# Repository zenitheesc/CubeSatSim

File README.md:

<h1 align="center" style="color:white; background-color:black">CubeSatSim</h1>

<a href="https://github.com/zenitheesc/CubeSatSim/tree/ZenithSatSim#-controle-"><h2> Controle </h2></a>

Para o controle destas placas podem ser utilizado um ESP32 Devkit V1 ou uma Raspberry Pi Zero.

ESP32 DevKit V1 (30 pinos)

-UART: GPIO1 (TX0) e GPIO3 (RX0)

-I2C: GPIO21 (SDA) e GPIO22 (SCL)

-SPI: GPIO12 (MISO), GPIO13 (MOSI), GPIO14 (SCK) e GPIO15 (CS)

Raspberry Pi Zero

-UART: GPIO14 (TX0) e GPIO15 (RX0)

-I2C: GPIO2 (SDA) e GPIO3 (SCL)

-SPI: GPIO9 (MISO), GPIO10 (MOSI), GPIO11 (SCK) e GPIO8 (CS)

Módulo Micro SD Card (comunicação SPI)

<a href="https://github.com/zenitheesc/CubeSatSim/tree/ZenithSatSim#comunica%C3%A7%C3%A3o-e-sensoriamento"><h2>Comunicação e Sensoriamento</h2></a>
E32-433T20DC Módulo LoRa

IMU6050 - Acelerômetro e Giroscópio (comunicação I2C)

BMP280 - Sensor de pressão e temperatura (comunicação I2C)

HDC1080 - Sensor de temperatura e umidade (comunicação I2C)

E32-433T20D - Módulo RF Wireless LoRa 433MHZ (comunicação UART)

<a href="https://github.com/zenitheesc/CubeSatSim/tree/ZenithSatSim#energia"><h2>Energia</h2></a>

LM2596 - Conversor Buck (3.3V)

LED  para indicar 3.3V

XL6009E1 - Conversor Boost (5V)

LED  para indicar 5V

TP4056 - Carregador da bateria

INA219 - Sensor de corrente e tensão DC (comunicação I2C)

Conector Borne para a bateria

Bateria de Litio (3.7V)

<a href="https://github.com/zenitheesc/CubeSatSim/tree/ZenithSatSim#energia"><h2>Lista de Componentes</h2></a>

<p align="center">

</p>
<p align = "center">

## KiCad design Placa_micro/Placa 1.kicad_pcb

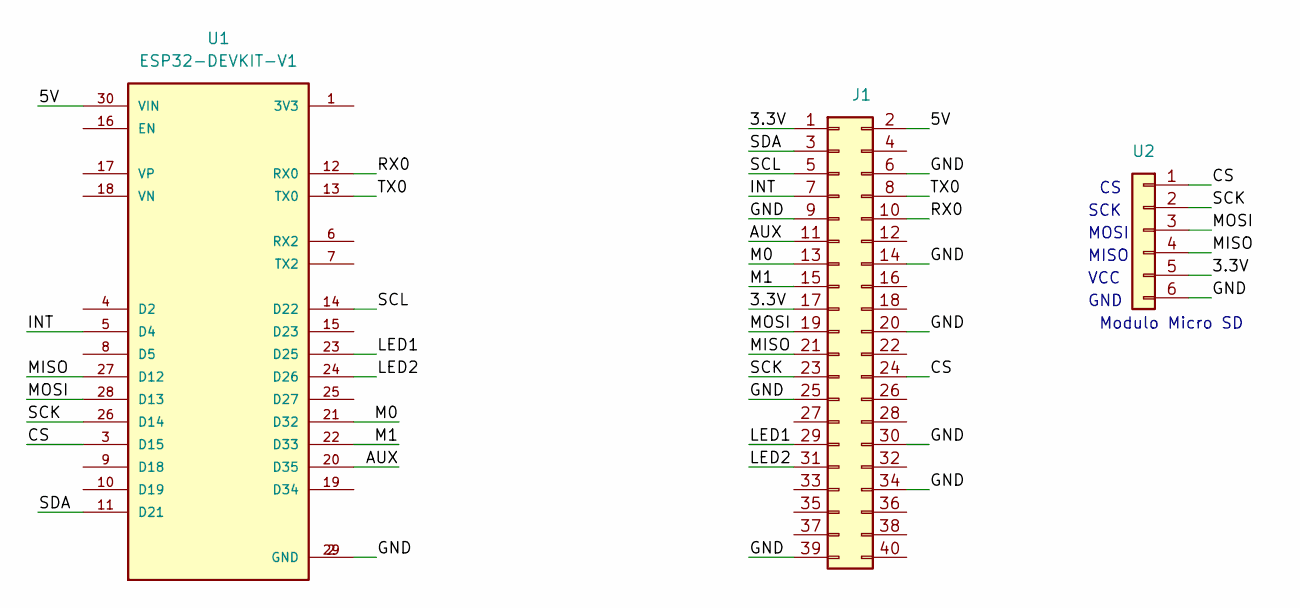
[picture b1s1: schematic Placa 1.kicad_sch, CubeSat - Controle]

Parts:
J1: Conn_02x20_Odd_Even; OBSAT-Board
U1: ESP32-DEVKIT-V1; ESP32_DEVKIT_V1_sem; PARTREV N/A
U2: Conn_01x06; PinSocket_1x06_P2.54mm_Horizontal

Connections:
/3.3V: J1.1, J1.17, U2.5
/5V: J1.2, U1.30 (VIN)
/AUX: J1.11, U1.20 (D35)
/CS: J1.24, U1.3 (D15), U2.1
/GND: J1.6, J1.9, J1.14, J1.20, J1.25, J1.30, J1.34, J1.39, U1.2 (GND), U1.29 (GND), U2.6
/INT: J1.7, U1.5 (D4)
/LED1: J1.29, U1.23 (D25)
/LED2: J1.31, U1.24 (D26)
/M0: J1.13, U1.21 (D32)
/M1: J1.15, U1.22 (D33)
/MISO: J1.21, U1.27 (D12), U2.4
/MOSI: J1.19, U1.28 (D13), U2.3
/RX0: J1.10, U1.12 (RX0)
/SCK: J1.23, U1.26 (D14), U2.2
/SCL: J1.5, U1.14 (D22)
/SDA: J1.3, U1.11 (D21)
/TX0: J1.8, U1.13 (TX0)

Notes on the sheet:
VCC
GND
Modulo Micro SD
MISO
SCK
MOSI

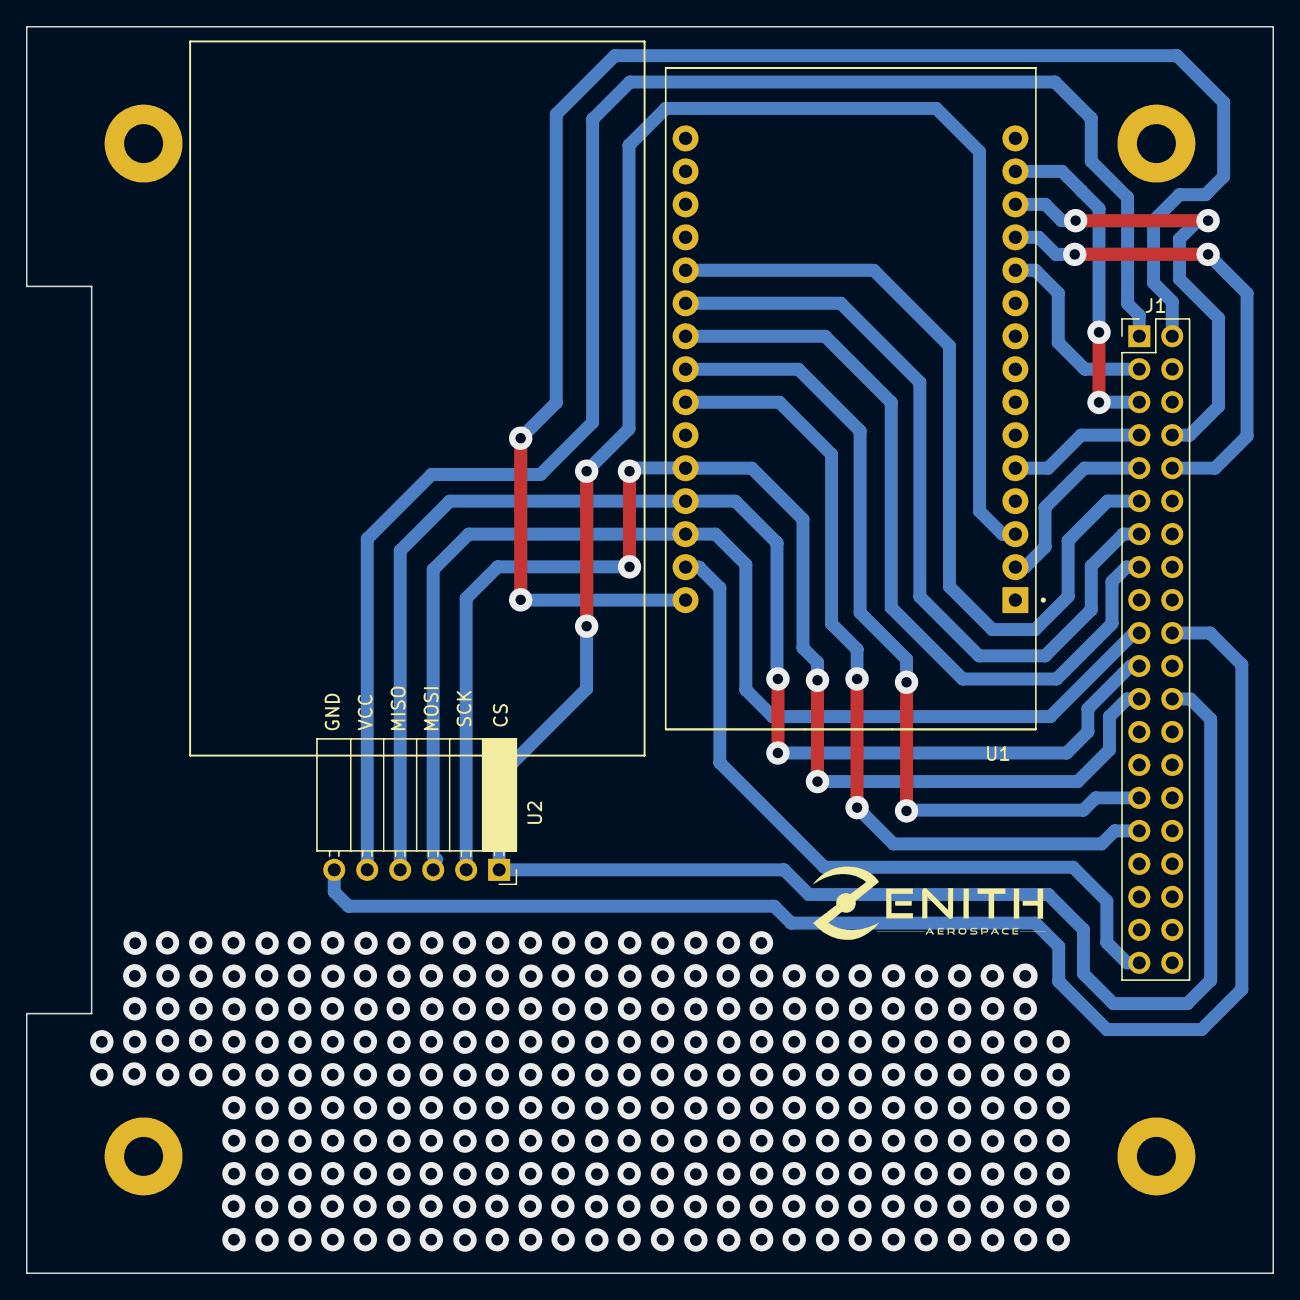
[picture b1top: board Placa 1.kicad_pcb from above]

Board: 2 copper layers, 96.0 x 96.0 mm, 3 parts (0 on the bottom side), 17 nets.

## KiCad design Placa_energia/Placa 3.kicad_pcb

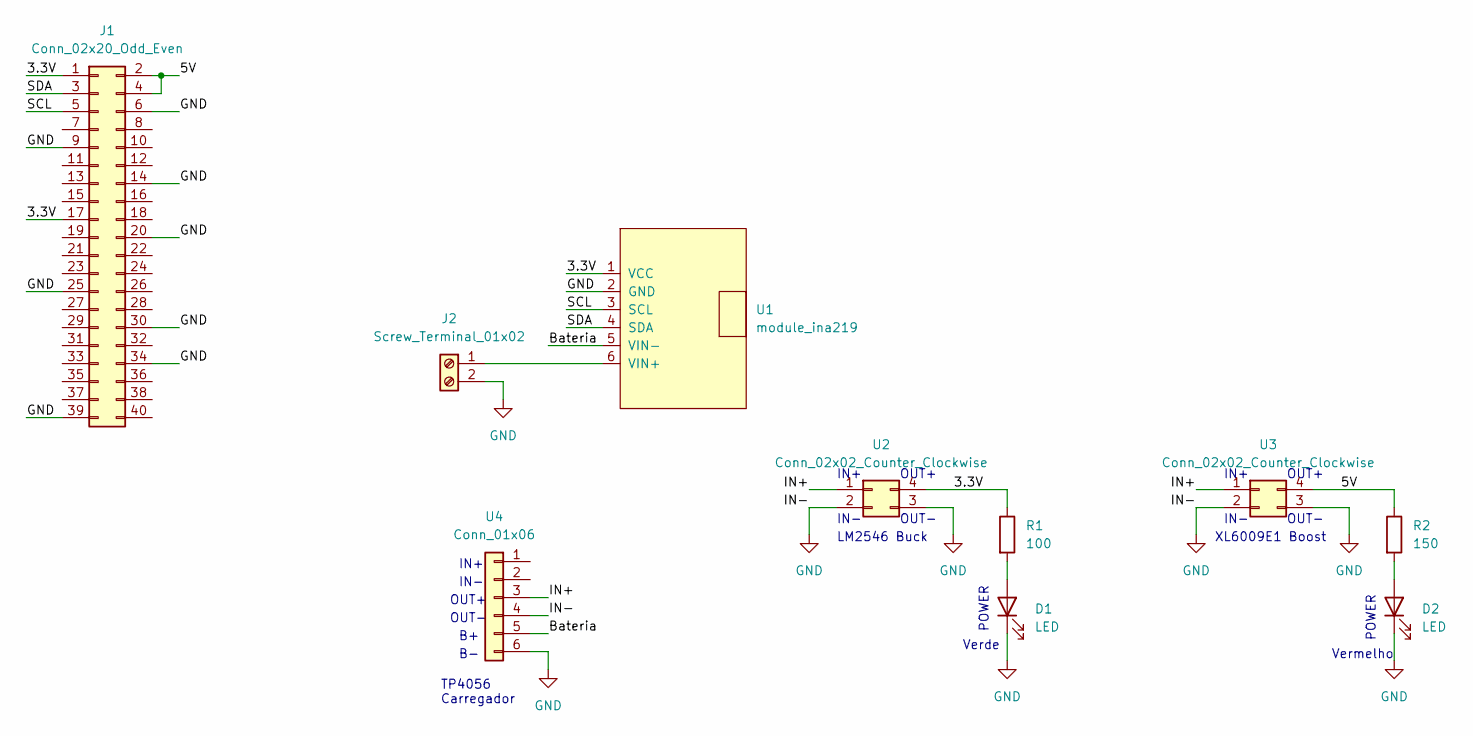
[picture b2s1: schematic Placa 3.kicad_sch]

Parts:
D1, D2: LED; LED_D5.0mm
J1: Conn_02x20_Odd_Even; OBSAT-Board
J2: Screw_Terminal_01x02; TerminalBlock_4Ucon_1x02_P3.50mm_Horizontal
R1: 100; R_Axial_DIN0204_L3.6mm_D1.6mm_P7.62mm_Horizontal
R2: 150; R_Axial_DIN0204_L3.6mm_D1.6mm_P7.62mm_Horizontal
U1: module_ina219
U2, U3: Conn_02x02_Counter_Clockwise; XL6009-Module
U4: Conn_01x06; TP4056-Module

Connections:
/3.3V: J1.1, J1.17, R1.1, U1.1 (VCC), U2.4
/5V: J1.2, J1.4, R2.1, U3.4
/Bateria: U1.5 (VIN-), U4.5
/IN+: U2.1, U3.1, U4.3
/SCL: J1.5, U1.3 (SCL)
/SDA: J1.3, U1.4 (SDA)
GND: D1.1 (K), D2.1 (K), J1.6, J1.9, J1.14, J1.20, J1.25, J1.30, J1.34, J1.39, J2.2, U1.2 (GND), U2.2, U2.3, U3.2, U3.3, U4.4, U4.6
unnamed: D1.2 (A), R1.2
unnamed: D2.2 (A), R2.2
unnamed: J2.1, U1.6 (VIN+)

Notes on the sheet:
Verde
Vermelho
OUT+
LM2546 Buck
POWER
XL6009E1 Boost
IN-
OUT-
IN+
TP4056 Carregador

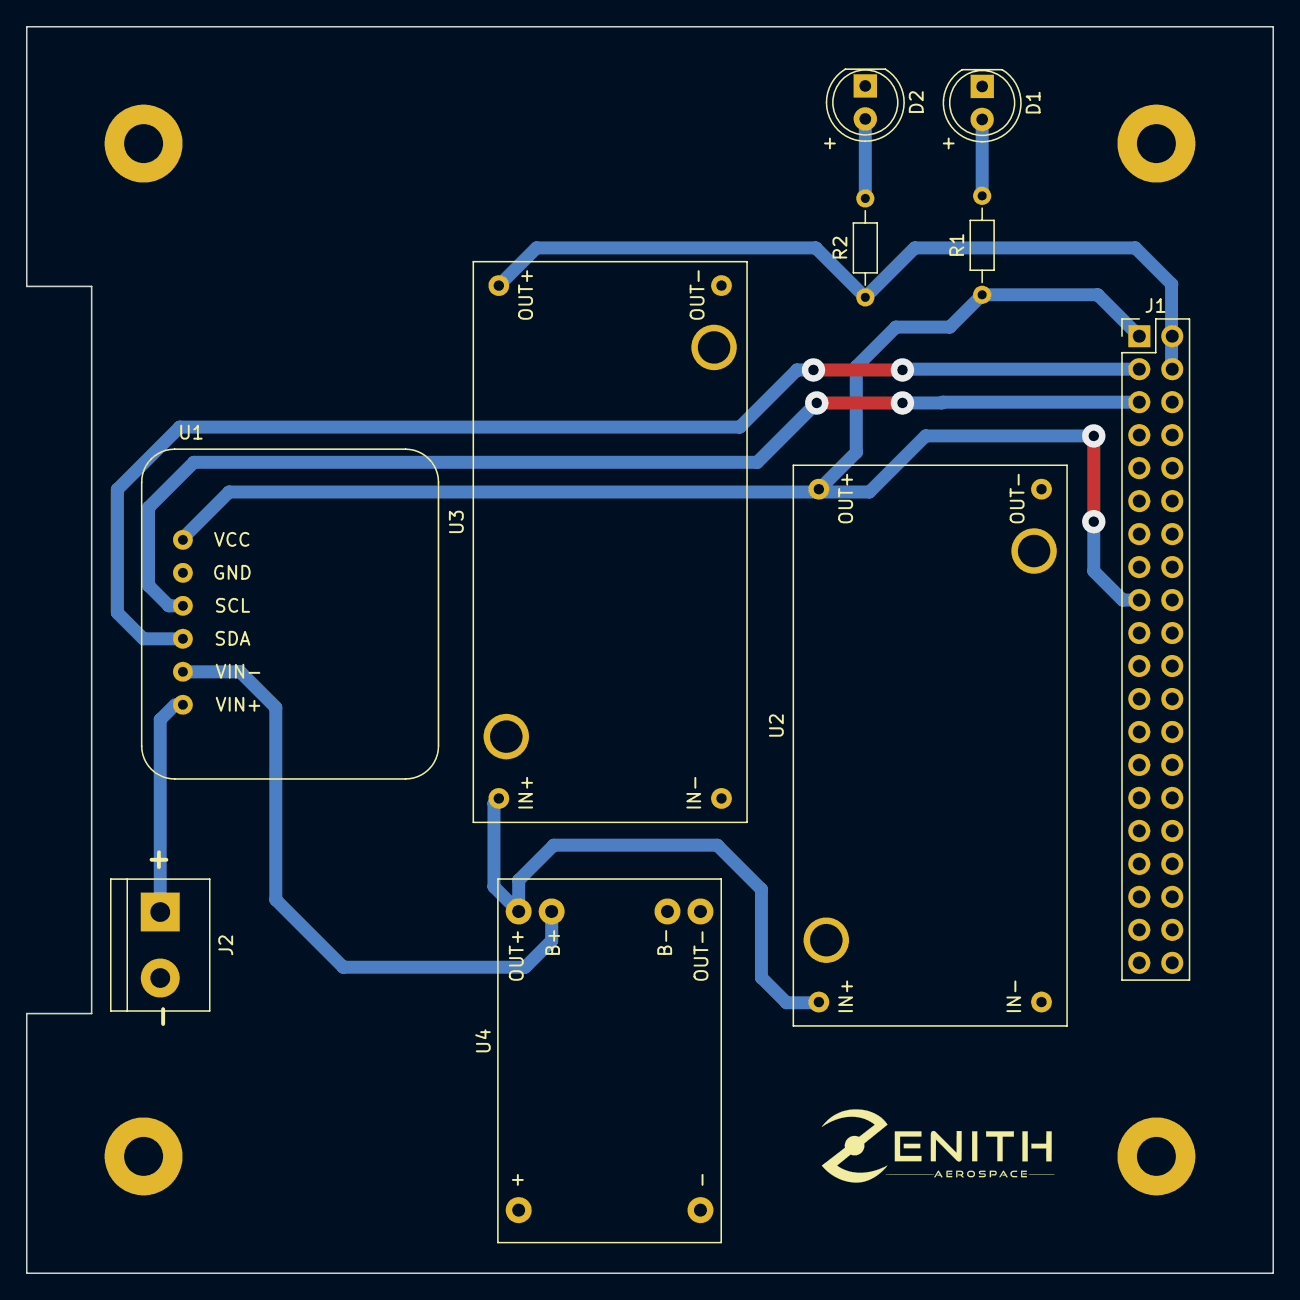
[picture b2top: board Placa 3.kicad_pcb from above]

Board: 2 copper layers, 96.0 x 96.0 mm, 10 parts (0 on the bottom side), 10 nets.

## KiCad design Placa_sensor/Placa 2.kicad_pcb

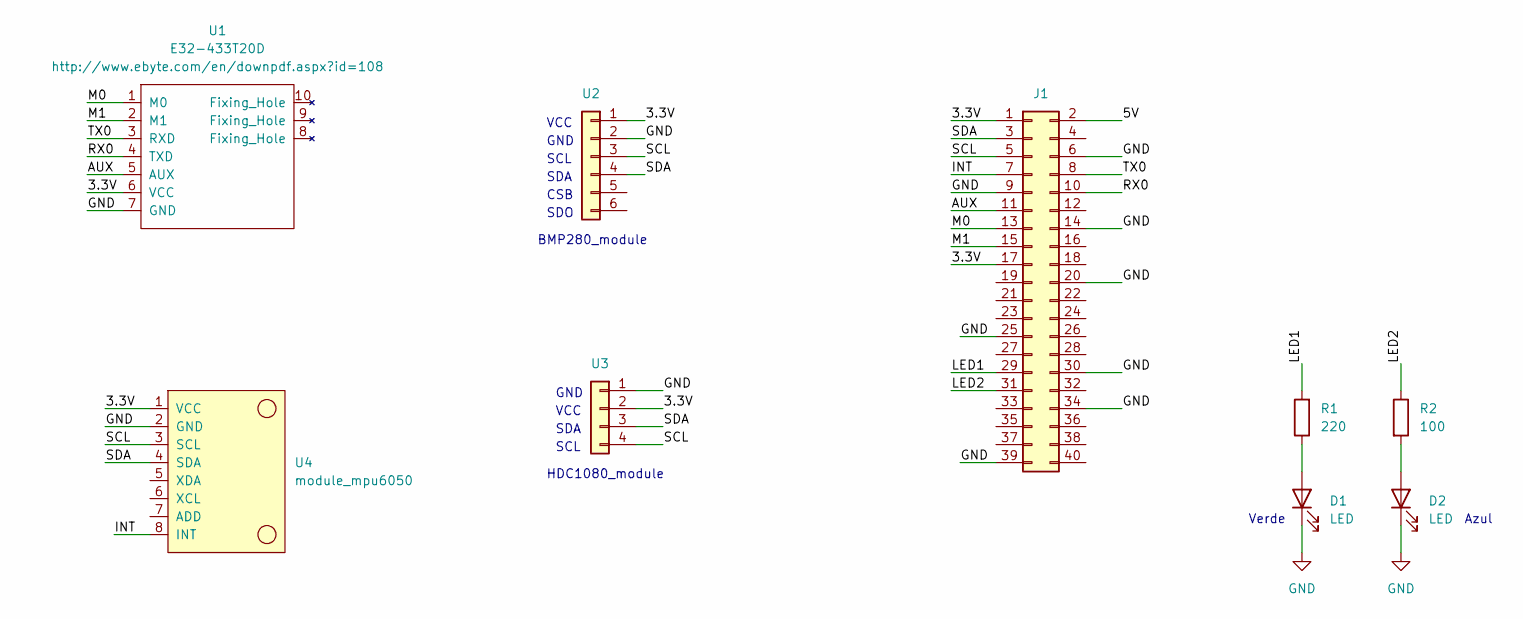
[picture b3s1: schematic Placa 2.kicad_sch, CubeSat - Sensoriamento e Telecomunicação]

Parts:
D1, D2: LED; LED_D5.0mm
J1: Conn_02x20_Odd_Even; OBSAT-Board
R1: 220; R_Axial_DIN0204_L3.6mm_D1.6mm_P7.62mm_Horizontal
R2: 100; R_Axial_DIN0204_L3.6mm_D1.6mm_P7.62mm_Horizontal
U1: E32-433T20D; E32-xxxT20D
U2: Conn_01x06; PinSocket_1x06_P2.54mm_Vertical
U3: Conn_01x04; PinSocket_1x04_P2.54mm_Vertical
U4: module_mpu6050

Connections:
/3.3V: J1.1, J1.17, U1.6 (VCC), U2.1, U3.2, U4.1 (VCC)
/5V: J1.2
/AUX: J1.11, U1.5 (AUX)
/INT: J1.7, U4.8 (INT)
/LED1: J1.29, R1.2
/LED2: J1.31, R2.1
/M0: J1.13, U1.1 (M0)
/M1: J1.15, U1.2 (M1)
/RX0: J1.10, U1.4 (TXD)
/SCL: J1.5, U2.3, U3.4, U4.3 (SCL)
/SDA: J1.3, U2.4, U3.3, U4.4 (SDA)
/TX0: J1.8, U1.3 (RXD)
GND: D1.1 (K), D2.1 (K), J1.6, J1.9, J1.14, J1.20, J1.25, J1.30, J1.34, J1.39, U1.7 (GND), U2.2, U3.1, U4.2 (GND)
unnamed: D1.2 (A), R1.1
unnamed: D2.2 (A), R2.2

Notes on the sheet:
SDO
CSB
SCL
SDA
BMP280_module
GND
HDC1080_module
VCC
Azul
Verde

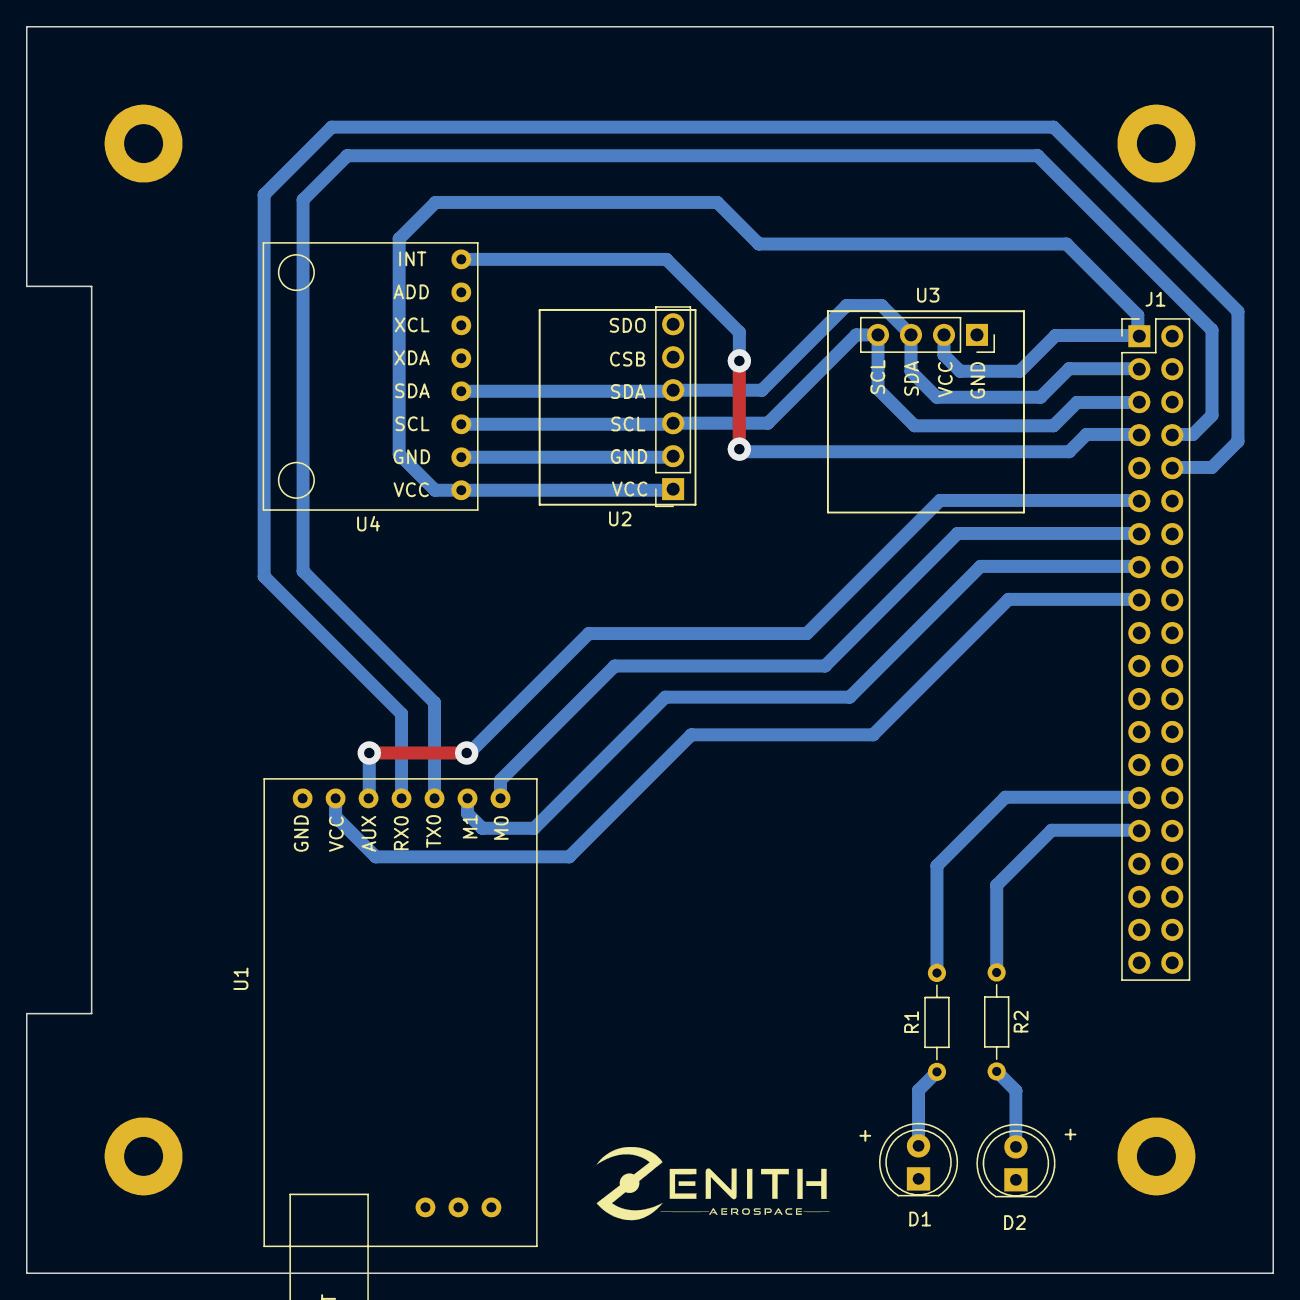
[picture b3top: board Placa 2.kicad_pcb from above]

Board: 2 copper layers, 96.0 x 96.0 mm, 9 parts (0 on the bottom side), 14 nets.

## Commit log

2023-10-31 Atualização das Placas
